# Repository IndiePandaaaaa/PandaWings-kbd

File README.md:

# PandaWings Keyboard

The PandaWings is a split keyboard with 3x5 column staggered keys with two 
additional keys on each side and with 3 thumb keys, based on 
[crkbd v3](https://github.com/foostan/crkbd/tree/v3-final).
Crkbd stands for Corne Keyboard.

## Idea

I wanted to create a corne compatible with the seeed xiao controller
instead of the pro-micro controllers. Due to missing pins for the matrix, 
the matrix is wired in a 4x5 grid and reshaped for thumb keys and two additional 
side keys. LEDs are permanent, toggleable with hardware switch. Per-key-RGB 
or display can be chosen while building.

## Lineup

- PandaWings v1 - Cherry MX switches: <br>
  Hotswappable Cherry MX switches, with LEDs, optional per-key-RGB or displays
- [PLANNED] PandaWings v2 - Cherry MX and Chocolate switches: <br>
  Hotswappable Cherry MX and Chocolate switches

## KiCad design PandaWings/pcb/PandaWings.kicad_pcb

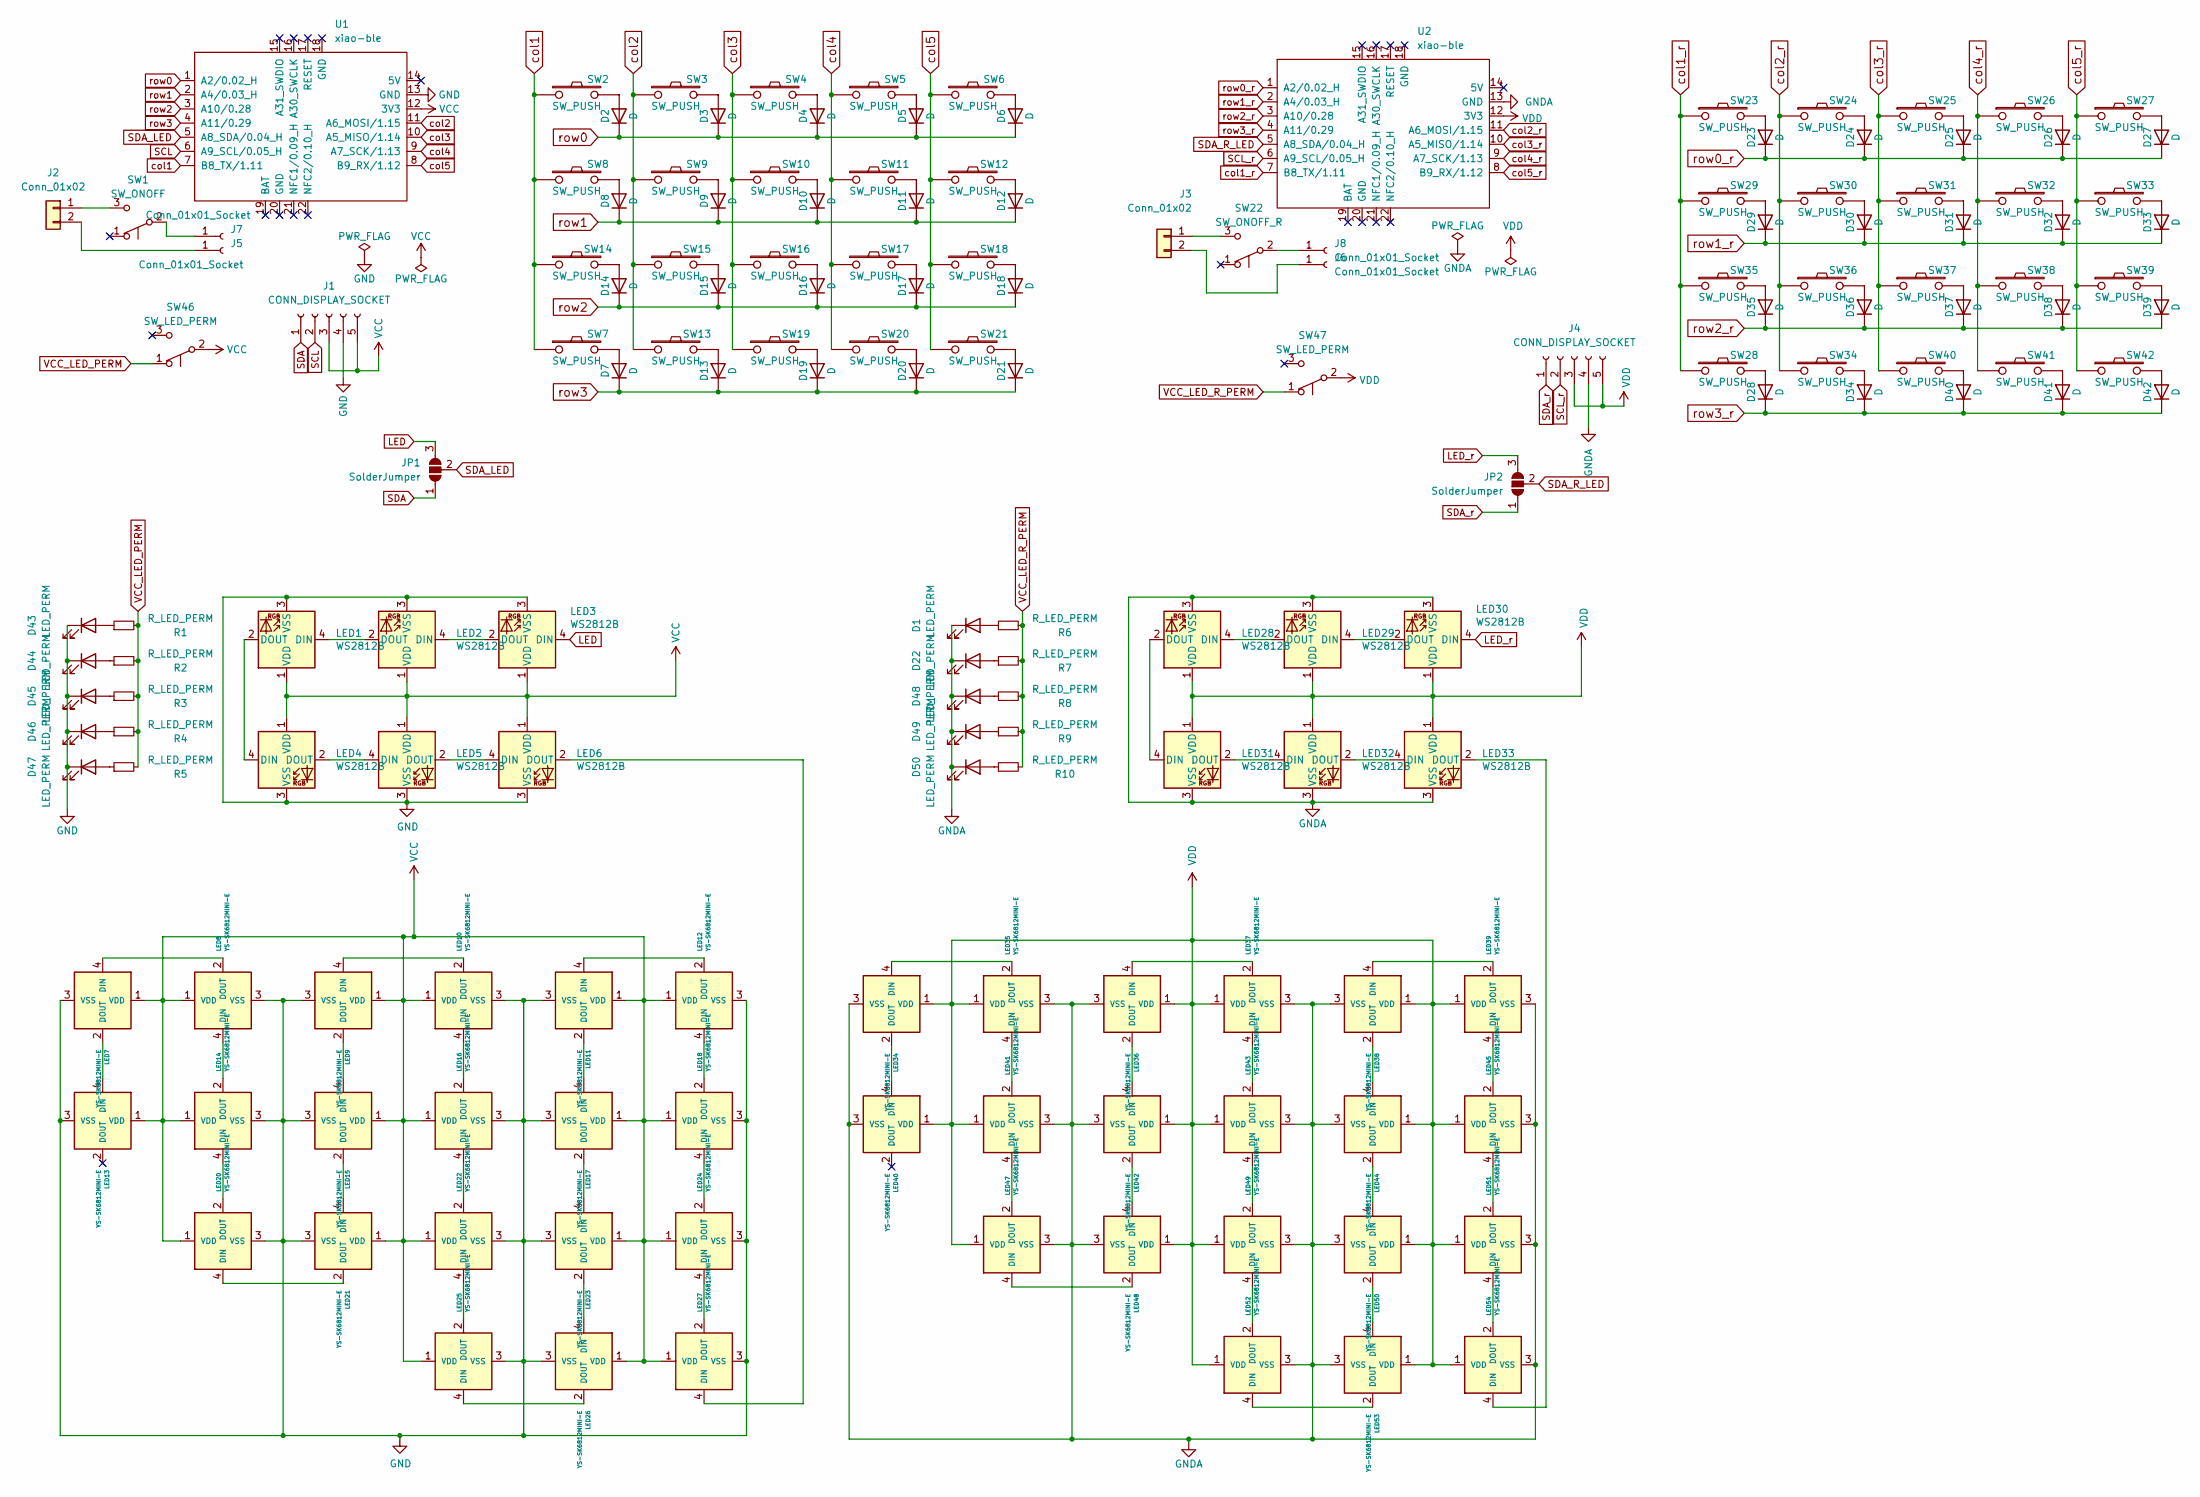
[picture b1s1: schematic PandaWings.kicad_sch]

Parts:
D1, D22, D43, D44, D45, D46, D47, D48, D49, D50: LED_PERM; LED_0603_1608Metric
D2, D3, D4, D5, D6, D7, D8, D9, D10, D11, D12, D13, D14, D15, D16, D17, D18, D19, D20, D21, D23, D24, D25, D26, D27, D28, D29, D30, D31, D32, D33, D34, D35, D36, D37, D38, D39, D40, D41, D42: D; D3_SMD_v2
J1, J4: CONN_DISPLAY_SOCKET; PinSocket_1x05_P2.54mm_Vertical
J2, J3: Conn_01x02; JST_PH_S2B-PH-K_1x02_P2.00mm_Horizontal
J5, J6, J7, J8: Conn_01x01_Socket; SolderJumper-2_P1.3mm_Bridged_RoundedPad1.0x1.5mm
JP1, JP2: SolderJumper; SolderJumper-3_P1.3mm_Open_Pad1.0x1.5mm_NumberLabels
LED1, LED2, LED3, LED4, LED5, LED6, LED28, LED29, LED30, LED31, LED32, LED33: WS2812B; LED_WS2812B_PLCC4_5.0x5.0mm_P3.2mm
LED7, LED8, LED9, LED10, LED11, LED12, LED13, LED14, LED15, LED16, LED17, LED18, LED20, LED21, LED22, LED23, LED24, LED25, LED26, LED27, LED34, LED35, LED36, LED37, LED38, LED39, LED40, LED41, LED42, LED43, LED44, LED45, LED47, LED48, LED49, LED50, LED51, LED52, LED53, LED54: YS-SK6812MINI-E
R1, R2, R3, R4, R5, R6, R7, R8, R9, R10: R_LED_PERM; R_0603_1608Metric
SW1: SW_ONOFF; SW_SPDT_PCM12
SW2, SW3, SW4, SW5, SW6, SW7, SW8, SW9, SW10, SW11, SW12, SW13, SW14, SW15, SW16, SW17, SW18, SW19, SW20, SW23, SW24, SW25, SW26, SW27, SW28, SW29, SW30, SW31, SW32, SW33, SW34, SW35, SW36, SW37, SW38, SW39, SW40, SW41: SW_PUSH; CherryMX_Hotswap
SW21, SW42: SW_PUSH; CherryMX_Hotswap_1.5u
SW22: SW_ONOFF_R; SW_SPDT_PCM12
SW46, SW47: SW_LED_PERM; SW_SPDT_PCM12
U1, U2: xiao-ble; XIAO-Generic-Thruhole-14P-2.54-21X17.8MM

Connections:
GND: D43.1 (K), D44.1 (K), D45.1 (K), D46.1 (K), D47.1 (K), J1.4, LED1.3 (VSS), LED2.3 (VSS), LED3.3 (VSS), LED4.3 (VSS), LED5.3 (VSS), LED6.3 (VSS), LED7.3 (VSS), LED8.3 (VSS), LED9.3 (VSS), LED10.3 (VSS), LED11.3 (VSS), LED12.3 (VSS), LED13.3 (VSS), LED14.3 (VSS), LED15.3 (VSS), LED16.3 (VSS), LED17.3 (VSS), LED18.3 (VSS), LED20.3 (VSS), LED21.3 (VSS), LED22.3 (VSS), LED23.3 (VSS), LED24.3 (VSS), LED25.3 (VSS), LED26.3 (VSS), LED27.3 (VSS), U1.13 (GND); also elsewhere on the board
GNDA: D1.1 (K), D22.1 (K), D48.1 (K), D49.1 (K), D50.1 (K), J4.4, LED28.3 (VSS), LED29.3 (VSS), LED30.3 (VSS), LED31.3 (VSS), LED32.3 (VSS), LED33.3 (VSS), LED34.3 (VSS), LED35.3 (VSS), LED36.3 (VSS), LED37.3 (VSS), LED38.3 (VSS), LED39.3 (VSS), LED40.3 (VSS), LED41.3 (VSS), LED42.3 (VSS), LED43.3 (VSS), LED44.3 (VSS), LED45.3 (VSS), LED47.3 (VSS), LED48.3 (VSS), LED49.3 (VSS), LED50.3 (VSS), LED51.3 (VSS), LED52.3 (VSS), LED53.3 (VSS), LED54.3 (VSS), U2.13 (GND); also elsewhere on the board
LED: JP1.3 (B), LED3.4 (DIN)
LED_r: JP2.3 (B), LED30.4 (DIN)
unnamed: D1.2 (A), R6.1
unnamed: D2.2 (A), SW2.2
unnamed: D3.2 (A), SW3.2
unnamed: D4.2 (A), SW4.2
unnamed: D5.2 (A), SW5.2
unnamed: D6.2 (A), SW6.2
unnamed: D7.2 (A), SW7.2
unnamed: D8.2 (A), SW8.2
unnamed: D9.2 (A), SW9.2
unnamed: D10.2 (A), SW10.2
unnamed: D11.2 (A), SW11.2
unnamed: D12.2 (A), SW12.2
unnamed: D13.2 (A), SW13.2
unnamed: D14.2 (A), SW14.2
unnamed: D15.2 (A), SW15.2
unnamed: D16.2 (A), SW16.2
unnamed: D17.2 (A), SW17.2
unnamed: D18.2 (A), SW18.2
unnamed: D19.2 (A), SW19.2
unnamed: D20.2 (A), SW20.2
unnamed: D21.2 (A), SW21.2
unnamed: D22.2 (A), R7.1
unnamed: D23.2 (A), SW23.2
unnamed: D24.2 (A), SW24.2
unnamed: D25.2 (A), SW25.2
unnamed: D26.2 (A), SW26.2
unnamed: D27.2 (A), SW27.2
unnamed: D28.2 (A), SW28.2
unnamed: D29.2 (A), SW29.2
unnamed: D30.2 (A), SW30.2
unnamed: D31.2 (A), SW31.2
unnamed: D32.2 (A), SW32.2
unnamed: D33.2 (A), SW33.2
unnamed: D34.2 (A), SW34.2
unnamed: D35.2 (A), SW35.2
unnamed: D36.2 (A), SW36.2
unnamed: D37.2 (A), SW37.2
unnamed: D38.2 (A), SW38.2
unnamed: D39.2 (A), SW39.2
unnamed: D40.2 (A), SW40.2
unnamed: D41.2 (A), SW41.2
unnamed: D42.2 (A), SW42.2
unnamed: D43.2 (A), R1.1
unnamed: D44.2 (A), R2.1
unnamed: D45.2 (A), R3.1
unnamed: D46.2 (A), R4.1
unnamed: D47.2 (A), R5.1
unnamed: D48.2 (A), R8.1
unnamed: D49.2 (A), R9.1
unnamed: D50.2 (A), R10.1
unnamed 54: J2.1, SW1.3 (C); also elsewhere on the board
unnamed: J2.2, J5.1
unnamed 56: J3.1, SW22.3 (C); also elsewhere on the board
unnamed: J3.2, J6.1
unnamed 58: J7.1, SW1.2 (B); also elsewhere on the board
unnamed 59: J8.1, SW22.2 (B); also elsewhere on the board
unnamed: LED1.4 (DIN), LED2.2 (DOUT)
unnamed: LED1.2 (DOUT), LED4.4 (DIN)
unnamed: LED2.4 (DIN), LED3.2 (DOUT)
unnamed: LED4.2 (DOUT), LED5.4 (DIN)
unnamed: LED5.2 (DOUT), LED6.4 (DIN)
unnamed: LED7.4 (DIN), LED8.2 (DOUT)
unnamed: LED10.4 (DIN), LED16.2 (DOUT)
unnamed: LED9.4 (DIN), LED10.2 (DOUT)
unnamed: LED11.4 (DIN), LED12.2 (DOUT)
unnamed: LED11.2 (DOUT), LED17.4 (DIN)
unnamed: LED12.4 (DIN), LED18.2 (DOUT)
unnamed: LED7.2 (DOUT), LED13.4 (DIN)
unnamed: LED14.4 (DIN), LED20.2 (DOUT)
unnamed: LED8.4 (DIN), LED14.2 (DOUT)
unnamed: LED9.2 (DOUT), LED15.4 (DIN)
unnamed: LED15.2 (DOUT), LED21.4 (DIN)
unnamed: LED16.4 (DIN), LED22.2 (DOUT)
unnamed: LED17.2 (DOUT), LED23.4 (DIN)
unnamed: LED18.4 (DIN), LED24.2 (DOUT)
unnamed: LED20.4 (DIN), LED21.2 (DOUT)
unnamed: LED22.4 (DIN), LED25.2 (DOUT)
unnamed: LED23.2 (DOUT), LED26.4 (DIN)
unnamed: LED24.4 (DIN), LED27.2 (DOUT)
unnamed: LED25.4 (DIN), LED26.2 (DOUT)
unnamed: LED6.2 (DOUT), LED27.4 (DIN)
unnamed: LED28.4 (DIN), LED29.2 (DOUT)
unnamed: LED28.2 (DOUT), LED31.4 (DIN)
unnamed: LED29.4 (DIN), LED30.2 (DOUT)
unnamed: LED31.2 (DOUT), LED32.4 (DIN)
unnamed: LED32.2 (DOUT), LED33.4 (DIN)
unnamed: LED33.2 (DOUT), LED54.4 (DIN)
unnamed: LED34.4 (DIN), LED35.2 (DOUT)
unnamed: LED34.2 (DOUT), LED40.4 (DIN)
unnamed: LED35.4 (DIN), LED41.2 (DOUT)
unnamed: LED36.4 (DIN), LED37.2 (DOUT)
unnamed: LED36.2 (DOUT), LED42.4 (DIN)
unnamed: LED37.4 (DIN), LED43.2 (DOUT)
unnamed: LED38.4 (DIN), LED39.2 (DOUT)
unnamed: LED38.2 (DOUT), LED44.4 (DIN)
unnamed: LED39.4 (DIN), LED45.2 (DOUT)
unnamed: LED41.4 (DIN), LED47.2 (DOUT)
unnamed: LED42.2 (DOUT), LED48.4 (DIN)
unnamed: LED43.4 (DIN), LED49.2 (DOUT)
unnamed: LED44.2 (DOUT), LED50.4 (DIN)
unnamed: LED45.4 (DIN), LED51.2 (DOUT)
unnamed: LED47.4 (DIN), LED48.2 (DOUT)
unnamed: LED49.4 (DIN), LED52.2 (DOUT)
unnamed: LED50.2 (DOUT), LED53.4 (DIN)
unnamed: LED51.4 (DIN), LED54.2 (DOUT)
unnamed: LED52.4 (DIN), LED53.2 (DOUT)
SCL: J1.2, U1.6 (A9_SCL/0.05_H); also elsewhere on the board
SCL_r: J4.2, U2.6 (A9_SCL/0.05_H); also elsewhere on the board
SDA: J1.1, JP1.1 (A)
SDA_LED: JP1.2 (C), U1.5 (A8_SDA/0.04_H); also elsewhere on the board
SDA_R_LED: JP2.2 (C), U2.5 (A8_SDA/0.04_H); also elsewhere on the board
SDA_r: J4.1, JP2.1 (A)
VCC: J1.3, J1.5, LED1.1 (VDD), LED2.1 (VDD), LED3.1 (VDD), LED4.1 (VDD), LED5.1 (VDD), LED6.1 (VDD), LED7.1 (VDD), LED8.1 (VDD), LED9.1 (VDD), LED10.1 (VDD), LED11.1 (VDD), LED12.1 (VDD), LED13.1 (VDD), LED14.1 (VDD), LED15.1 (VDD), LED16.1 (VDD), LED17.1 (VDD), LED18.1 (VDD), LED20.1 (VDD), LED21.1 (VDD), LED22.1 (VDD), LED23.1 (VDD), LED24.1 (VDD), LED25.1 (VDD), LED26.1 (VDD), LED27.1 (VDD), SW46.2 (B), U1.12 (3V3); also elsewhere on the board
VCC_LED_PERM: R1.2, R2.2, R3.2, R4.2, R5.2, SW46.1 (A); also elsewhere on the board
VCC_LED_R_PERM: R6.2, R7.2, R8.2, R9.2, R10.2, SW47.1 (A); also elsewhere on the board
VDD: J4.3, J4.5, LED28.1 (VDD), LED29.1 (VDD), LED30.1 (VDD), LED31.1 (VDD), LED32.1 (VDD), LED33.1 (VDD), LED34.1 (VDD), LED35.1 (VDD), LED36.1 (VDD), LED37.1 (VDD), LED38.1 (VDD), LED39.1 (VDD), LED40.1 (VDD), LED41.1 (VDD), LED42.1 (VDD), LED43.1 (VDD), LED44.1 (VDD), LED45.1 (VDD), LED47.1 (VDD), LED48.1 (VDD), LED49.1 (VDD), LED50.1 (VDD), LED51.1 (VDD), LED52.1 (VDD), LED53.1 (VDD), LED54.1 (VDD), SW47.2 (B), U2.12 (3V3); also elsewhere on the board
col1: SW2.1, SW7.1, SW8.1, SW14.1, U1.7 (B8_TX/1.11); also elsewhere on the board
col1_r: SW23.1, SW28.1, SW29.1, SW35.1, U2.7 (B8_TX/1.11); also elsewhere on the board
col2: SW3.1, SW9.1, SW13.1, SW15.1, U1.11 (A6_MOSI/1.15); also elsewhere on the board
col2_r: SW24.1, SW30.1, SW34.1, SW36.1, U2.11 (A6_MOSI/1.15); also elsewhere on the board
col3: SW4.1, SW10.1, SW16.1, SW19.1, U1.10 (A5_MISO/1.14); also elsewhere on the board
col3_r: SW25.1, SW31.1, SW37.1, SW40.1, U2.10 (A5_MISO/1.14); also elsewhere on the board
col4: SW5.1, SW11.1, SW17.1, SW20.1, U1.9 (A7_SCK/1.13); also elsewhere on the board
col4_r: SW26.1, SW32.1, SW38.1, SW41.1, U2.9 (A7_SCK/1.13); also elsewhere on the board
col5: SW6.1, SW12.1, SW18.1, SW21.1, U1.8 (B9_RX/1.12); also elsewhere on the board
col5_r: SW27.1, SW33.1, SW39.1, SW42.1, U2.8 (B9_RX/1.12); also elsewhere on the board
row0: D2.1 (K), D3.1 (K), D4.1 (K), D5.1 (K), D6.1 (K), U1.1 (A2/0.02_H); also elsewhere on the board
row0_r: D23.1 (K), D24.1 (K), D25.1 (K), D26.1 (K), D27.1 (K), U2.1 (A2/0.02_H); also elsewhere on the board
row1: D8.1 (K), D9.1 (K), D10.1 (K), D11.1 (K), D12.1 (K), U1.2 (A4/0.03_H); also elsewhere on the board
row1_r: D29.1 (K), D30.1 (K), D31.1 (K), D32.1 (K), D33.1 (K), U2.2 (A4/0.03_H); also elsewhere on the board
row2: D14.1 (K), D15.1 (K), D16.1 (K), D17.1 (K), D18.1 (K), U1.3 (A10/0.28); also elsewhere on the board
row2_r: D35.1 (K), D36.1 (K), D37.1 (K), D38.1 (K), D39.1 (K), U2.3 (A10/0.28); also elsewhere on the board
row3: D7.1 (K), D13.1 (K), D19.1 (K), D20.1 (K), D21.1 (K), U1.4 (A11/0.29); also elsewhere on the board
row3_r: D28.1 (K), D34.1 (K), D40.1 (K), D41.1 (K), D42.1 (K), U2.4 (A11/0.29); also elsewhere on the board

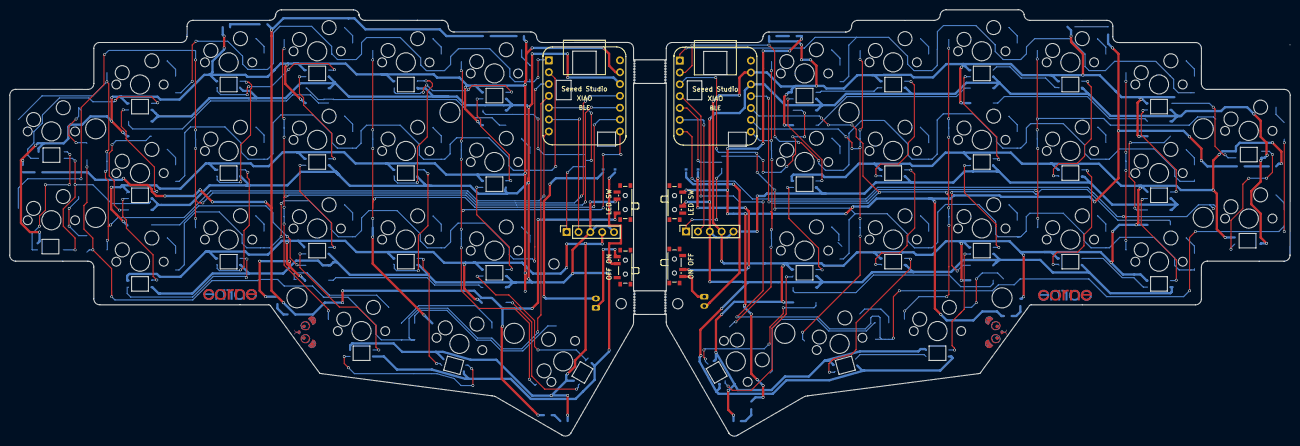
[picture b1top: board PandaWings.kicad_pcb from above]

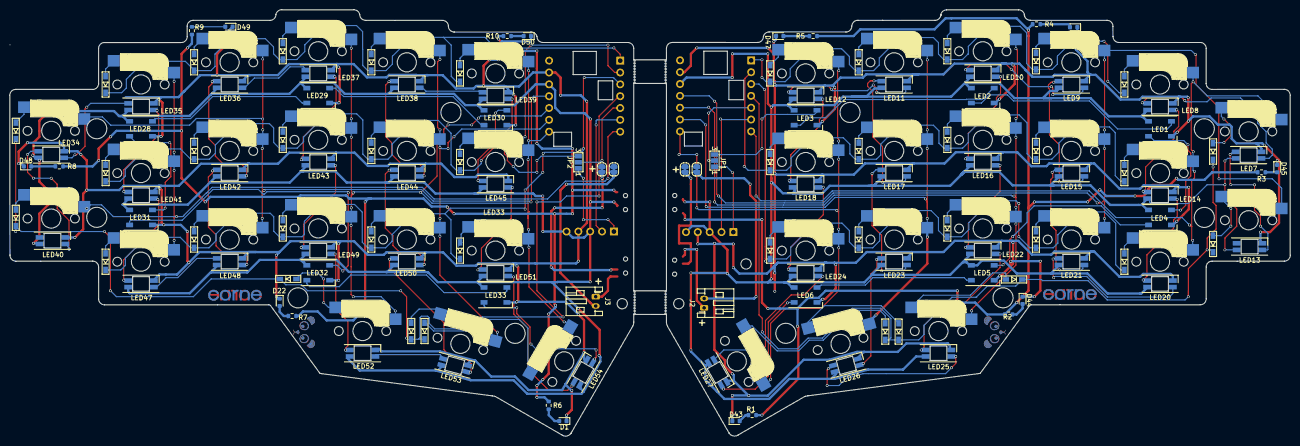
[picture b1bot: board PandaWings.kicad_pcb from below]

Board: 2 copper layers, 274.6 x 91.4 mm, 181 parts (122 on the bottom side), 138 nets.

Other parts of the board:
BLE: xiao-ble; XIAO-Generic-Thruhole-14P-2.54-21X17.8MM
BLE#2: xiao-ble; XIAO-Generic-Thruhole-14P-2.54-21X17.8MM
LED SW: SW_LED_PERM; SW_SPDT_PCM12
LED SW#2: SW_LED_PERM; SW_SPDT_PCM12
OFF ON: SW_ONOFF; SW_SPDT_PCM12
ON OFF: SW_ONOFF_R; SW_SPDT_PCM12
Ref**: Val**; M2_HOLE_v2
Ref**#2, Ref**#3, Ref**#4, Ref**#5, Ref**#6, Ref**#7, Ref**#8, Ref**#9, Ref**#10, Ref**#11, Ref**#12, Ref**#13: Val**; M2_HOLE_v2

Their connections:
GND: BLE#2.13 (GND); also elsewhere on the board
GNDA: BLE.13 (GND); also elsewhere on the board
unnamed 54: OFF ON.3 (C); also elsewhere on the board
unnamed 56: ON OFF.3 (C); also elsewhere on the board
unnamed 58: OFF ON.2 (B); also elsewhere on the board
unnamed 59: ON OFF.2 (B); also elsewhere on the board
SCL: BLE#2.6 (A9_SCL/0.05_H); also elsewhere on the board
SCL_r: BLE.6 (A9_SCL/0.05_H); also elsewhere on the board
SDA_LED: BLE#2.5 (A8_SDA/0.04_H); also elsewhere on the board
SDA_R_LED: BLE.5 (A8_SDA/0.04_H); also elsewhere on the board
VCC: BLE#2.12 (3V3), LED SW#2.2 (B); also elsewhere on the board
VCC_LED_PERM: LED SW#2.1 (A); also elsewhere on the board
VCC_LED_R_PERM: LED SW.1 (A); also elsewhere on the board
VDD: BLE.12 (3V3), LED SW.2 (B); also elsewhere on the board
col1: BLE#2.7 (B8_TX/1.11); also elsewhere on the board
col1_r: BLE.7 (B8_TX/1.11); also elsewhere on the board
col2: BLE#2.11 (A6_MOSI/1.15); also elsewhere on the board
col2_r: BLE.11 (A6_MOSI/1.15); also elsewhere on the board
col3: BLE#2.10 (A5_MISO/1.14); also elsewhere on the board
col3_r: BLE.10 (A5_MISO/1.14); also elsewhere on the board
col4: BLE#2.9 (A7_SCK/1.13); also elsewhere on the board
col4_r: BLE.9 (A7_SCK/1.13); also elsewhere on the board
col5: BLE#2.8 (B9_RX/1.12); also elsewhere on the board
col5_r: BLE.8 (B9_RX/1.12); also elsewhere on the board
row0: BLE#2.1 (A2/0.02_H); also elsewhere on the board
row0_r: BLE.1 (A2/0.02_H); also elsewhere on the board
row1: BLE#2.2 (A4/0.03_H); also elsewhere on the board
row1_r: BLE.2 (A4/0.03_H); also elsewhere on the board
row2: BLE#2.3 (A10/0.28); also elsewhere on the board
row2_r: BLE.3 (A10/0.28); also elsewhere on the board
row3: BLE#2.4 (A11/0.29); also elsewhere on the board
row3_r: BLE.4 (A11/0.29); also elsewhere on the board

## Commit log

2024-01-09 corne-cherry.kicad_sch: changed the components in the circuit diagram to make the corne fit the seeed xiao ble.
2024-02-11 finished track routing.
2024-02-11 .gitignore: added gbr/ and report.txt.
2024-02-12 corne-cherry.kicad_pcb: fixed some DRCs and rerouted some tracks.
2024-02-26 removed corne-classic and corne-light, renamed corne-cherry to PandaWings and corne-chocolate to PandaWings-LP
2024-02-26 renamed project files for PandaWings.
2024-02-26 removed corne cases.
2024-02-26 removed corne firmware guide.
2024-02-28 PandaWings: added revision text on schematic and pcb.
2024-03-01 added case/PandaWings.scad, firstly with case for the dongle.
2024-03-02 added vektor files for pcb.
2024-03-04 added helping sketches for the case design.
2024-03-04 added vektor geometries for case construction.
2024-03-04 PandaWings.scad: added model for switch plate.
2024-03-04 removed corne vector files.
2024-03-05 added vector ressources for the case.
2024-03-05 moved case vectors into case folder.
2024-03-05 added STL for switch plates with M3 screws.
2024-03-05 added sub parts from the existing svgs.
2024-03-05 PandaWings-Edge_Cuts_half_square_outer.svg: cleaned up content.
2024-03-05 restructured svgs for the case.
2024-03-05 PandaWings.scad: fixed faulty svg paths due to renaming.
2024-03-06 renamed to better fitting names.
2024-03-06 fixed orientation.
2024-03-06 fixed size to be common with the other vectors.
2024-03-06 PandaWings.scad: added first sample for the case.
2024-03-07 PandaWings.scad: added surface for pcb to sit on.
2024-03-07 fixed position of the cutouts.
2024-03-07 PandaWings.scad: added tenting holes.
2024-03-09 fixed position of the cutouts and added version with pcb for orientation.
2024-03-09 PandaWings.scad: fixed postition of the standoffs.
2024-03-09 PandaWings_SwitchPlates_M3.stl: fixed mounting diameter.
2024-03-09 added case stl and fixed naming.
2024-03-09 PandaWings_SwitchPlates_M3.stl: fixed mounting positions and added battery slot.
2024-03-10 PandaWings.scad: added mounting option for later wrist rest.
2024-03-14 added vector for the wrist rest.
2024-03-14 added vector for
    wrist rest without case.
2024-03-26 PandaWings.scad: added caps for the tenting screws.
2024-03-26 PandaWings.scad: moved all components to be generated individually.
2024-03-26 added PandaWings tenting caps.
2024-03-28 added DES Keycap repo.
2024-03-28 updated DES repo.
2024-03-28 added initial version for PandaWings Keycaps.
2024-03-29 added code for all the different keycaps for PandaWings.
2024-05-13 .gitignore: added .idea to be ignored.
2024-05-13 Keycaps: fixed travel height blocker, added stl with all caps.
2024-05-13 Keycaps: added individual stl files for the different keys.
2024-05-15 Keycaps: added caps for glorious panda switches.
2024-08-13 PandaWings.scad: added tenting sockets to mount the keyboard with tripod helpers to a table.
2024-08-13 updated stl files according to changes in PandaWings.scad.
2024-08-13 updated README.md.
2024-08-13 README.md: added line breaks.
2024-12-21 case: added tenting option.
2024-12-21 keycaps: renamed variables.
2024-12-21 pcb: updated version.
2024-12-21 keycaps: trying to fix pressing stop.
2024-12-21 des: updated to latest commit.
2024-12-21 keycaps: added travel_stop to keys caps.
2024-12-21 keycaps: fixed broken supports.
2024-12-23 keycaps: changed the stem diameter to 5.7mm for the glorious switches.
2024-12-23 keycaps: changed the keycaps to an universal model with travel stop rings.
2024-12-26 keycaps: updated stl models.
2024-12-27 keycaps: removed travelstop due to incompatibility issues.
2024-12-27 keycaps: updated stls.
